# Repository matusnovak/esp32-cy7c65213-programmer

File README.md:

# ESP32 USB-C programmer with CY7C65213

This is a simple USB-C programmer that uses the CY7C65213 UART bridge controller. This repository contains KiCad 6 project files with gerber files exported. This board is capable of DTR and RTS, therefore the program upload experience should be without any problem.

**[Schematic PDF](esp32-cy7c65213-programmer.pdf)**

## NOTE

* Do not connect a capacitor on the BOOT pin (GPIO 0 pin) towards the ground. It will cause the ESP32 to jump to the programming mode on power up.
* Use 1uF capacitor between the ESP32 reset pin (also known as EN or PN pin) between it and the ground. You will also need 10K pull-up resistor between that same reset pin and the + 3.3V.
* The Rx, Tx, Boot, and En pins on this board are 3.3V tolerant only.
* The Rx LED may start blinking or stay up. This is due to Rx picking up noise and treating it as a signal if nothing is connected to the Rx.

## Connection schematic

Use the following schematic to connect this programmer to ESP32

## Drivers

* Windows: [Link to the manufacturer Infineon](https://www.infineon.com/cms/en/design-support/tools/sdk/usb-controllers-sdk/usb-serial-software-development-kit/?utm_source=cypress&utm_medium=referral&utm_campaign=202110_globe_en_all_integration-software)
* Linux: Works out of the box, no driver needed, any recent Kernel is fine, it will appear at `/dev/ttyACM0`.
* MacOS: Should work out of the box.

## Why CY7C65213?

It works in Linux out of the box without the need to install any drivers (it needs a driver on Windows). Compared to the CH340 UART controller, the drivers for CY7C65213 are stable and mature. I do not want to install some shady CH340 drivers that work half of the time and randomly disconnect.

## Programming (platformio)

If you are using platformio for programming, you can use the following example below:

```ini
[env:esp32s3]
platform = espressif32        # Required
board = adafruit_feather_esp32s3_nopsram # Required, or choose similar
framework = espidf            # Or "arduino", your choice.
upload_port = /dev/ttyACM0    # Or COM3 or similar for Windows
board_build.flash_mode = dio  # Might be needed for a successful upload to ESP32-S3
monitor_port = /dev/ttyACM0   # Or COM3 or similar for Windows
monitor_speed = 115200        # This is the default value
```

## Programming (Arduino)

Simply choose the correct COM port from the top menu bar, and use the Adafruit Feather ESP32 board. (It should work with any board).

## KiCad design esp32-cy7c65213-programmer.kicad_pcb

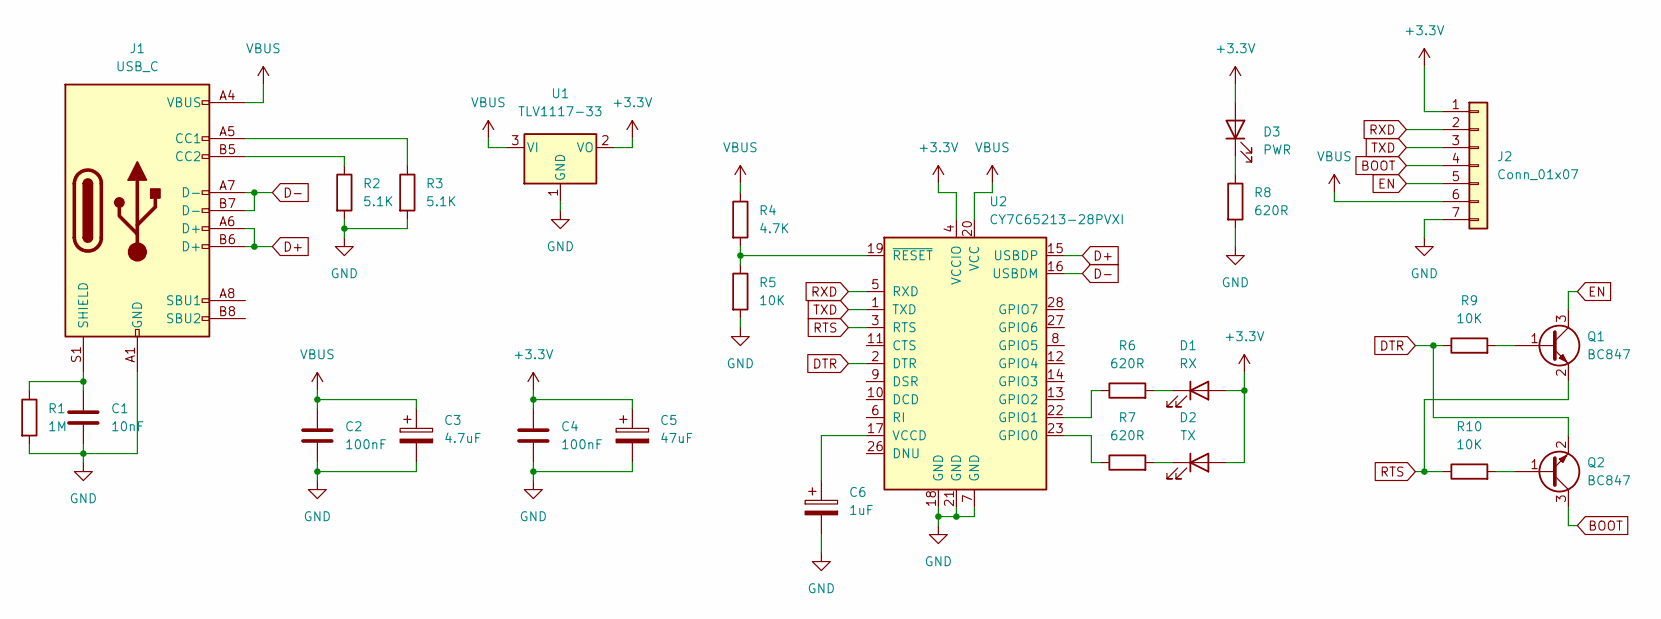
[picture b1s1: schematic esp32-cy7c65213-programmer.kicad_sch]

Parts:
C1: 10nF; C_1206_3216Metric_Pad1.33x1.80mm_HandSolder
C2, C4: 100nF; C_1206_3216Metric_Pad1.33x1.80mm_HandSolder
C3: 4.7uF; CP_EIA-3216-12_Kemet-S_Pad1.58x1.35mm_HandSolder
C5: 47uF; C_Elec_6.3x5.4
C6: 1uF; CP_EIA-3216-12_Kemet-S_Pad1.58x1.35mm_HandSolder
D1: RX; LED_1206_3216Metric_Pad1.42x1.75mm_HandSolder
D2: TX; LED_1206_3216Metric_Pad1.42x1.75mm_HandSolder
D3: PWR; LED_1206_3216Metric_Pad1.42x1.75mm_HandSolder
J1: USB_C; USB_C_Receptacle_HRO_TYPE-C-31-M-12
J2: Conn_01x07; PinHeader_1x07_P2.54mm_Horizontal
Q1, Q2: BC847; SOT-23_Handsoldering
R1: 1M; R_1206_3216Metric_Pad1.30x1.75mm_HandSolder
R2, R3: 5.1K; R_1206_3216Metric_Pad1.30x1.75mm_HandSolder
R4: 4.7K; R_1206_3216Metric_Pad1.30x1.75mm_HandSolder
R5, R9, R10: 10K; R_1206_3216Metric_Pad1.30x1.75mm_HandSolder
R6, R7, R8: 620R; R_1206_3216Metric_Pad1.30x1.75mm_HandSolder
U1: TLV1117-33; TO-252-3_TabPin2
U2: CY7C65213-28PVXI; SSOP-28_5.3x10.2mm_P0.65mm

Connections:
+3.3V: C4.1, C5.1, D1.2 (A), D2.2 (A), D3.2 (A), J2.1, U1.2 (VO), U2.4 (VCCIO)
BOOT: J2.4, Q2.3 (C)
D+: J1.A6 (D+), J1.B6 (D+), U2.15 (USBDP)
D-: J1.A7 (D-), J1.B7 (D-), U2.16 (USBDM)
DTR: Q2.2 (E), R9.1, U2.2 (DTR)
EN: J2.5, Q1.3 (C)
GND: C1.2, C2.2, C3.2, C4.2, C5.2, C6.2, J1.A1 (GND), J1.A12 (GND), J1.B1 (GND), J1.B12 (GND), J2.7, R1.2, R2.2, R3.2, R5.2, R8.2, U1.1 (GND), U2.7 (GND), U2.18 (GND), U2.21 (GND)
unnamed: C1.1, J1.S1 (SHIELD), R1.1
unnamed: C6.1, U2.17 (VCCD)
unnamed: D1.1 (K), R6.2
unnamed: D2.1 (K), R7.2
unnamed: D3.1 (K), R8.1
unnamed: J1.A5 (CC1), R3.1
unnamed: J1.B5 (CC2), R2.1
unnamed: R4.2, R5.1, U2.19 (~RESET)
unnamed: R6.1, U2.22 (GPIO1)
unnamed: R7.1, U2.23 (GPIO0)
unnamed: Q1.1 (B), R9.2
unnamed: Q2.1 (B), R10.2
RTS: Q1.2 (E), R10.1, U2.3 (RTS)
RXD: J2.2, U2.5 (RXD)
TXD: J2.3, U2.1 (TXD)
VBUS: C2.1, C3.1, J1.A4 (VBUS), J1.A9 (VBUS), J1.B4 (VBUS), J1.B9 (VBUS), J2.6, R4.1, U1.3 (VI), U2.20 (VCC)

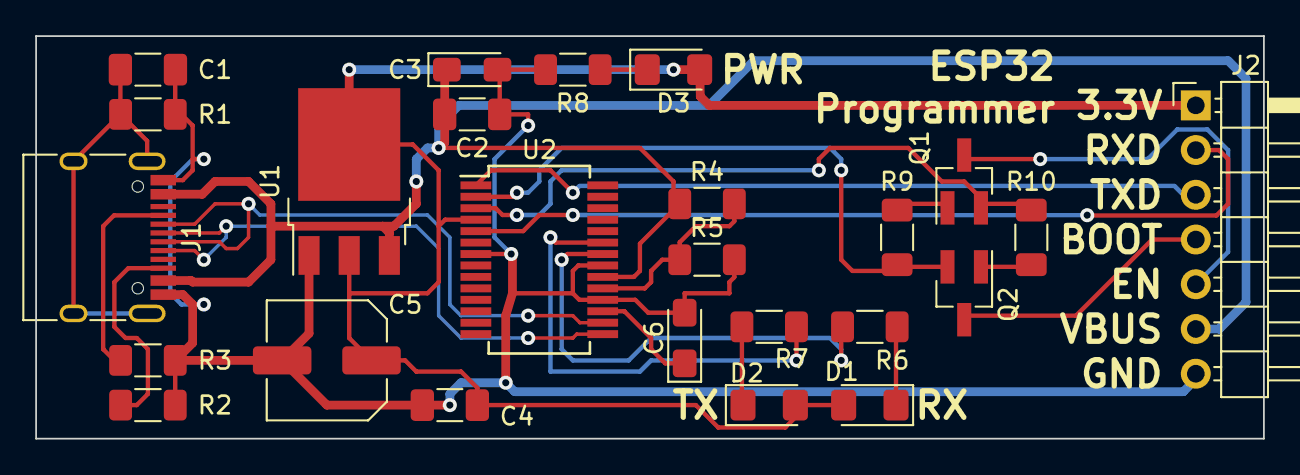
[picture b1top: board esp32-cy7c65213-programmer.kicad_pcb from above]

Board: 2 copper layers, 69.7 x 22.9 mm, 25 parts (0 on the bottom side), 23 nets.

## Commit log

2022-11-25 Update readme with screenshot
2022-11-25 Update readme with schematic and programming instructions
2022-11-25 Add schematic PDF
2022-12-24 Fix wrong transistor type and update the screenshots
2022-12-24 Update the PDF with the latest schematic
